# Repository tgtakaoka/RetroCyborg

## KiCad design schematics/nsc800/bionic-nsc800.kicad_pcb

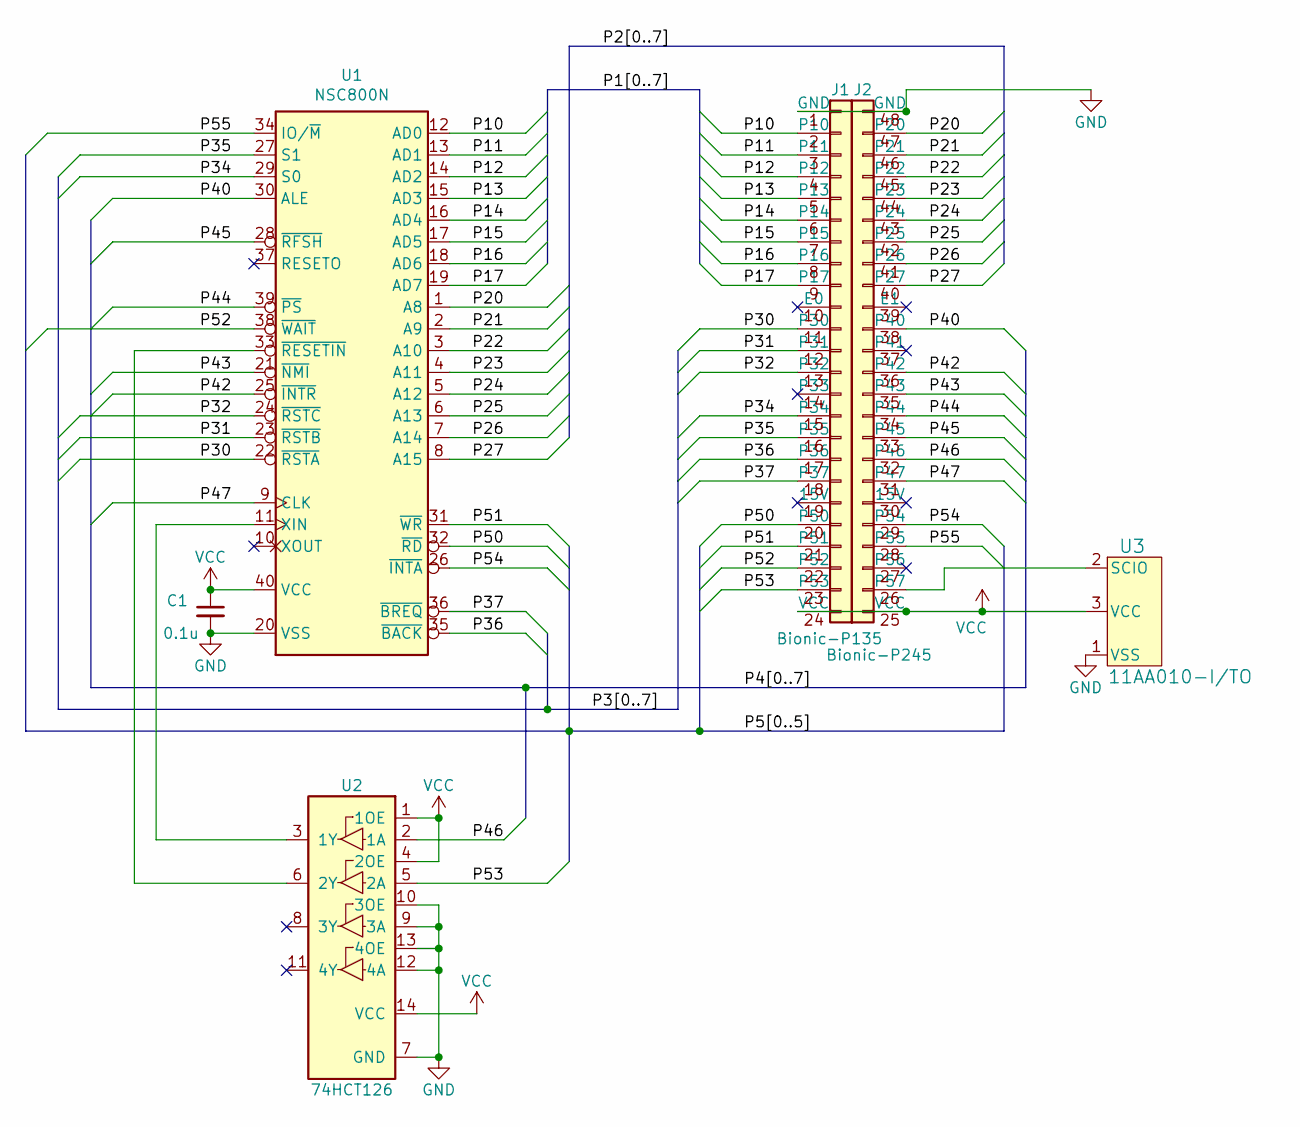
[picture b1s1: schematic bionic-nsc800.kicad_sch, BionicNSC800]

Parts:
C1: 0.1u; C_Disc_D3.4mm_W2.1mm_P2.50mm
J1: Bionic-P135; Bionic-P135_Vertical
J2: Bionic-P245; Bionic-P245_Vertical
U1: NSC800N; DIP-40_W15.24mm
U2: 74HCT126; DIP-14_W7.62mm
U3: 11AA010-I/TO; TO-92_MC_MCH

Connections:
/P10: J1.2 (P10), U1.12 (AD0)
/P11: J1.3 (P11), U1.13 (AD1)
/P12: J1.4 (P12), U1.14 (AD2)
/P13: J1.5 (P13), U1.15 (AD3)
/P14: J1.6 (P14), U1.16 (AD4)
/P15: J1.7 (P15), U1.17 (AD5)
/P16: J1.8 (P16), U1.18 (AD6)
/P17: J1.9 (P17), U1.19 (AD7)
/P20: J2.47 (P20), U1.1 (A8)
/P21: J2.46 (P21), U1.2 (A9)
/P22: J2.45 (P22), U1.3 (A10)
/P23: J2.44 (P23), U1.4 (A11)
/P24: J2.43 (P24), U1.5 (A12)
/P25: J2.42 (P25), U1.6 (A13)
/P26: J2.41 (P26), U1.7 (A14)
/P27: J2.40 (P27), U1.8 (A15)
/P30: J1.11 (P30), U1.22 (~RSTA)
/P31: J1.12 (P31), U1.23 (~RSTB)
/P32: J1.13 (P32), U1.24 (~RSTC)
/P34: J1.15 (P34), U1.29 (S0)
/P35: J1.16 (P35), U1.27 (S1)
/P36: J1.17 (P36), U1.35 (~BACK)
/P37: J1.18 (P37), U1.36 (~BREQ)
/P40: J2.38 (P40), U1.30 (ALE)
/P42: J2.36 (P42), U1.25 (~INTR)
/P43: J2.35 (P43), U1.21 (~NMI)
/P44: J2.34 (P44), U1.39 (~PS)
/P45: J2.33 (P45), U1.28 (~RFSH)
/P46: J2.32 (P46), U2.2 (1A)
/P47: J2.31 (P47), U1.9 (CLK)
/P50: J1.20 (P50), U1.32 (~RD)
/P51: J1.21 (P51), U1.31 (~WR)
/P52: J1.22 (P52), U1.38 (~WAIT)
/P53: J1.23 (P53), U2.5 (2A)
/P54: J2.29 (P54), U1.26 (~INTA)
/P55: J2.28 (P55), U1.34 (IO/~M)
GND: C1.2, J1.1 (GND), J2.48 (GND), U1.20 (VSS), U2.7 (GND), U2.9 (3A), U2.10 (3OE), U2.12 (4A), U2.13 (4OE), U3.1 (VSS)
unnamed: J2.26 (P57), U3.2 (SCIO)
unnamed: U1.11 (XIN), U2.3 (1Y)
unnamed: U1.33 (~RESETIN), U2.6 (2Y)
VCC: C1.1, J1.24 (VCC), J2.25 (VCC), U1.40 (VCC), U2.1 (1OE), U2.4 (2OE), U2.14 (VCC), U3.3 (VCC)

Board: 2 copper layers, 10 parts (0 on the bottom side), 41 nets, no tracks yet.

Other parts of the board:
MH1, MH2, MH3, MH4: MountingHole_3.2mm_M3

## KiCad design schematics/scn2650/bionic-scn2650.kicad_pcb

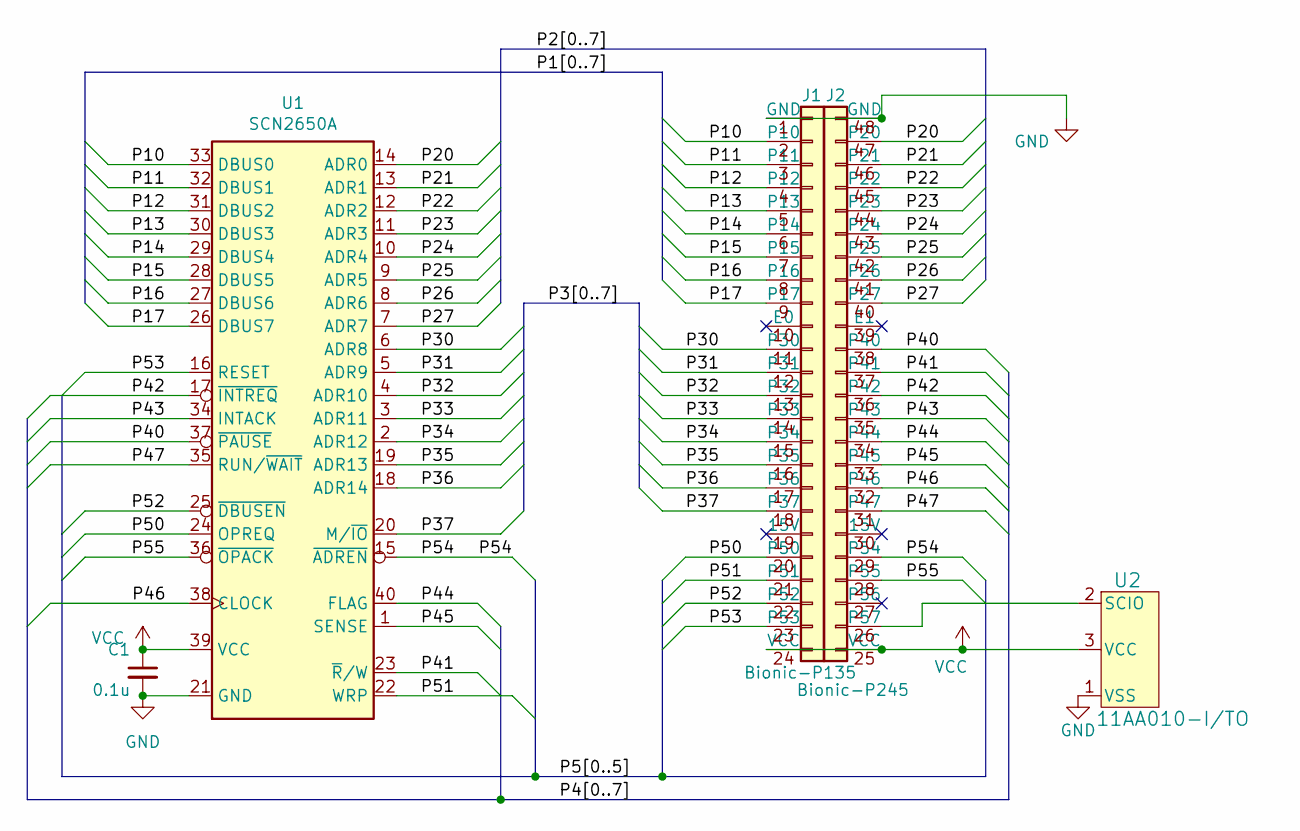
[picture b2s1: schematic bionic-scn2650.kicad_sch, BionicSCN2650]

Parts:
C1: 0.1u; C_Disc_D3.4mm_W2.1mm_P2.50mm
J1: Bionic-P135; Bionic-P135_Vertical
J2: Bionic-P245; Bionic-P245_Vertical
U1: SCN2650A; DIP-40_W15.24mm
U2: 11AA010-I/TO; TO-92_MC_MCH

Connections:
/P10: J1.2 (P10), U1.33 (DBUS0)
/P11: J1.3 (P11), U1.32 (DBUS1)
/P12: J1.4 (P12), U1.31 (DBUS2)
/P13: J1.5 (P13), U1.30 (DBUS3)
/P14: J1.6 (P14), U1.29 (DBUS4)
/P15: J1.7 (P15), U1.28 (DBUS5)
/P16: J1.8 (P16), U1.27 (DBUS6)
/P17: J1.9 (P17), U1.26 (DBUS7)
/P20: J2.47 (P20), U1.14 (ADR0)
/P21: J2.46 (P21), U1.13 (ADR1)
/P22: J2.45 (P22), U1.12 (ADR2)
/P23: J2.44 (P23), U1.11 (ADR3)
/P24: J2.43 (P24), U1.10 (ADR4)
/P25: J2.42 (P25), U1.9 (ADR5)
/P26: J2.41 (P26), U1.8 (ADR6)
/P27: J2.40 (P27), U1.7 (ADR7)
/P30: J1.11 (P30), U1.6 (ADR8)
/P31: J1.12 (P31), U1.5 (ADR9)
/P32: J1.13 (P32), U1.4 (ADR10)
/P33: J1.14 (P33), U1.3 (ADR11)
/P34: J1.15 (P34), U1.2 (ADR12)
/P35: J1.16 (P35), U1.19 (ADR13)
/P36: J1.17 (P36), U1.18 (ADR14)
/P37: J1.18 (P37), U1.20 (M/~IO)
/P40: J2.38 (P40), U1.37 (~PAUSE)
/P41: J2.37 (P41), U1.23 (~R/W)
/P42: J2.36 (P42), U1.17 (~INTREQ)
/P43: J2.35 (P43), U1.34 (INTACK)
/P44: J2.34 (P44), U1.40 (FLAG)
/P45: J2.33 (P45), U1.1 (SENSE)
/P46: J2.32 (P46), U1.38 (CLOCK)
/P47: J2.31 (P47), U1.35 (RUN/~WAIT)
/P50: J1.20 (P50), U1.24 (OPREQ)
/P51: J1.21 (P51), U1.22 (WRP)
/P52: J1.22 (P52), U1.25 (~DBUSEN)
/P53: J1.23 (P53), U1.16 (RESET)
/P54: J2.29 (P54), U1.15 (~ADREN)
/P55: J2.28 (P55), U1.36 (~OPACK)
GND: C1.2, J1.1 (GND), J2.48 (GND), U1.21 (GND), U2.1 (VSS)
unnamed: J2.26 (P57), U2.2 (SCIO)
VCC: C1.1, J1.24 (VCC), J2.25 (VCC), U1.39 (VCC), U2.3 (VCC)

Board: 2 copper layers, 9 parts (0 on the bottom side), 41 nets, no tracks yet.

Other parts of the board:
MH1, MH2, MH3, MH4: MountingHole_3.2mm_M3
